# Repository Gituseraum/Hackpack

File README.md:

# Hackpack
Hackpad I designed to hopefully run doom on
PCB
Here's a picture of my schematic! I wired a xiao rp204 module to a TFT display, 2 LEDs, a and 4 switches, 

Schematic	PCB

[ x ] I ran DRC in KiCad and have made sure there are 0 errors!

Scematic overview

CAD Model:
Everything fits together using 4 M3 Heatset inserts and 4 M3x16mm screws. Here's how it looks:

It was made in fusion360 pretty nifty stuff.

Part BOM:

1x xiao at $4.30/per. 

1x PCB from JLCPCB

$2 for 5x + $1.50 shipping

4x Blank DSA keycaps (LCSC) $0.44 (min order 5)

4x MX-Style switches

1x0.91 inch OLED displays

4x M3x16mm screws

4x M3x5mx4mm heatset inserts

3d Printed parts- useing my printer

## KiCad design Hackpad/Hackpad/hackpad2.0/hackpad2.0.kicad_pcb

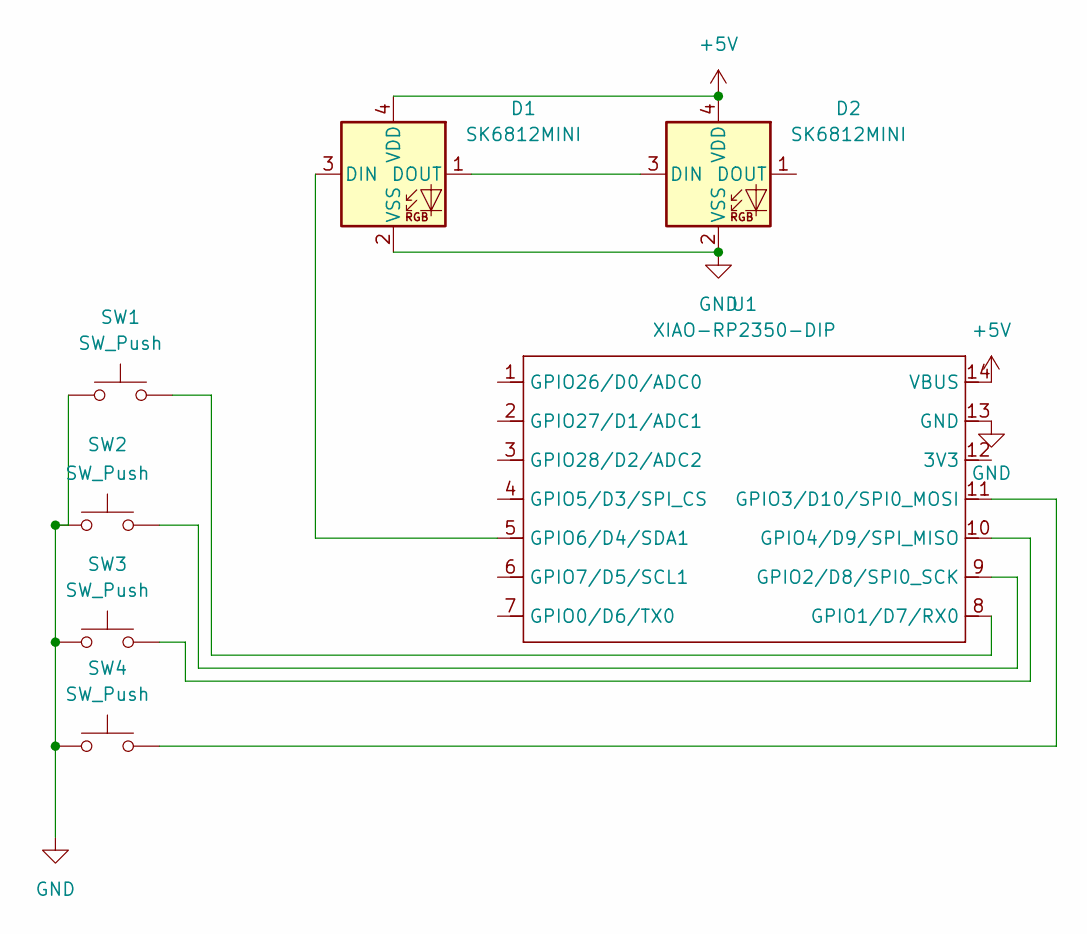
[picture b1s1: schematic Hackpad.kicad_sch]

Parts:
D1, D2: SK6812MINI; LED_SK6812MINI_PLCC4_3.5x3.5mm_P1.75mm
SW1, SW2, SW3, SW4: SW_Push; SW_Cherry_MX_1.00u_PCB
U1: XIAO-RP2350-DIP; MOUDLE14P-XIAO-DIP-SMD

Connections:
+5V: D1.4 (VDD), D2.4 (VDD), U1.14 (5V); also elsewhere on the board
GND: D1.2 (VSS), D2.2 (VSS), SW1.1, SW2.1, SW3.1, SW4.1, U1.13 (GND); also elsewhere on the board
unnamed: D1.3 (DIN), U1.5 (GPIO6_D4_SDA)
unnamed: D1.1 (DOUT), D2.3 (DIN)
unnamed 4: U1.1 (GPIO26_A0_D0); also elsewhere on the board
unnamed 5: U1.2 (GPIO27_A1_D1); also elsewhere on the board
unnamed: SW1.2, U1.8 (GPIO1_D7_CSn_RX)
unnamed: SW2.2, U1.9 (GPIO2_D8_SCK)
unnamed: SW4.2, U1.11 (GPIO3_D10_MOSI)
unnamed: SW3.2, U1.10 (GPIO4_D9_MISO)

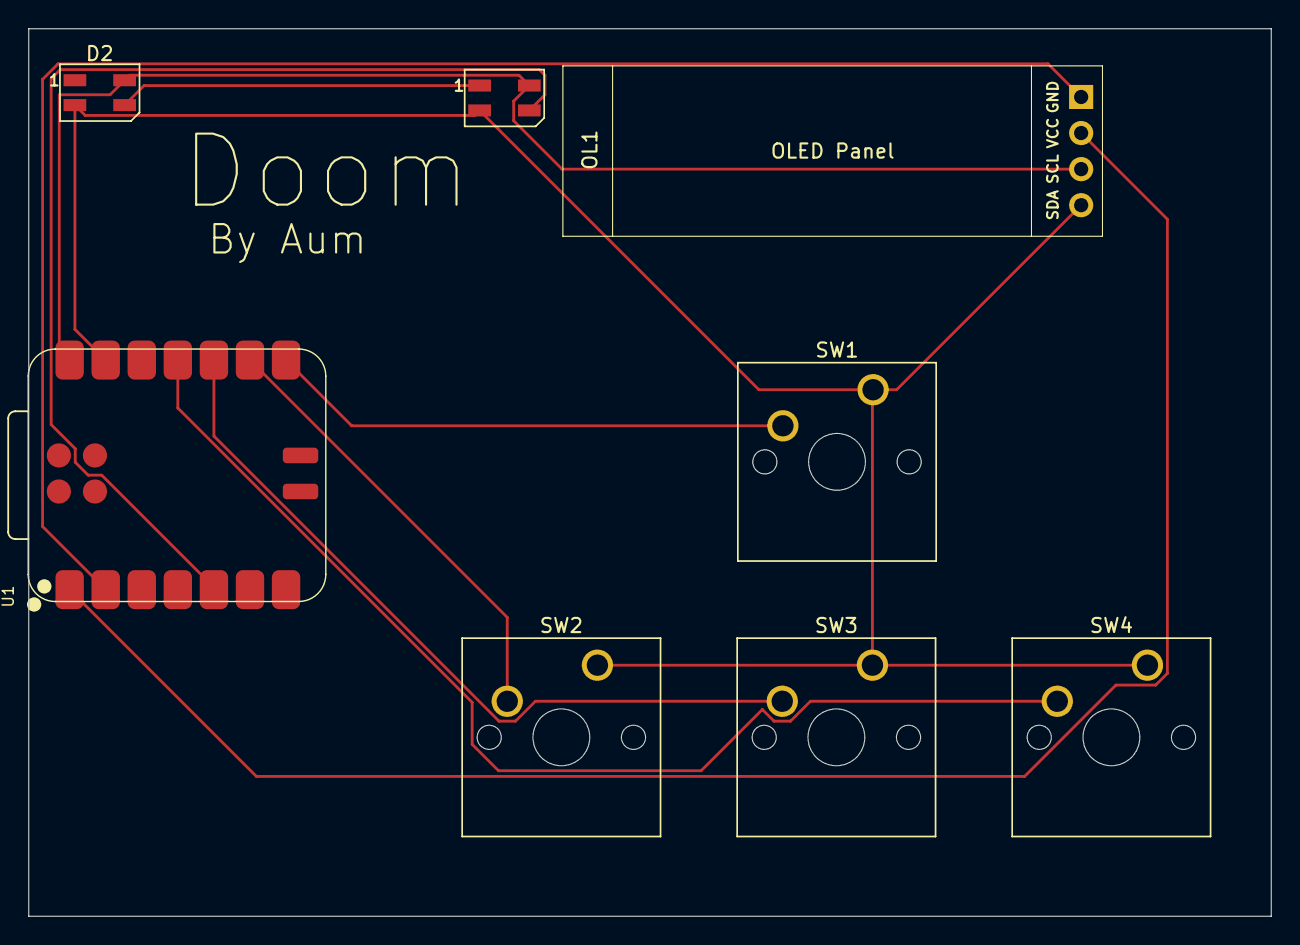
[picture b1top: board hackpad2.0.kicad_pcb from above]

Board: 2 copper layers, 87.5 x 62.5 mm, 8 parts (0 on the bottom side), 10 nets.

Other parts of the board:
OL1: OLED; SSD1306-0.91-OLED-4pin-128x32

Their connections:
+5V: OL1.3 (VCC); also elsewhere on the board
GND: OL1.4 (GND); also elsewhere on the board
unnamed 4: OL1.2 (SCL); also elsewhere on the board
unnamed 5: OL1.1 (SDA); also elsewhere on the board

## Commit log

2025-12-05 firmware
2025-12-05 Update firmware
2025-12-11 Rename hackpac.f3z to CAD
2025-12-11 Create PCB
